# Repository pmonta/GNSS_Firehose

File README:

Design files for a wideband GNSS front-end board.  Digitizes three 50 MHz RF channels, emits 2-bit samples to gigabit Ethernet (~800 Mbit/s total payload).  Includes schematic, PCB layout, HDL, and software.  Open-source licensing.

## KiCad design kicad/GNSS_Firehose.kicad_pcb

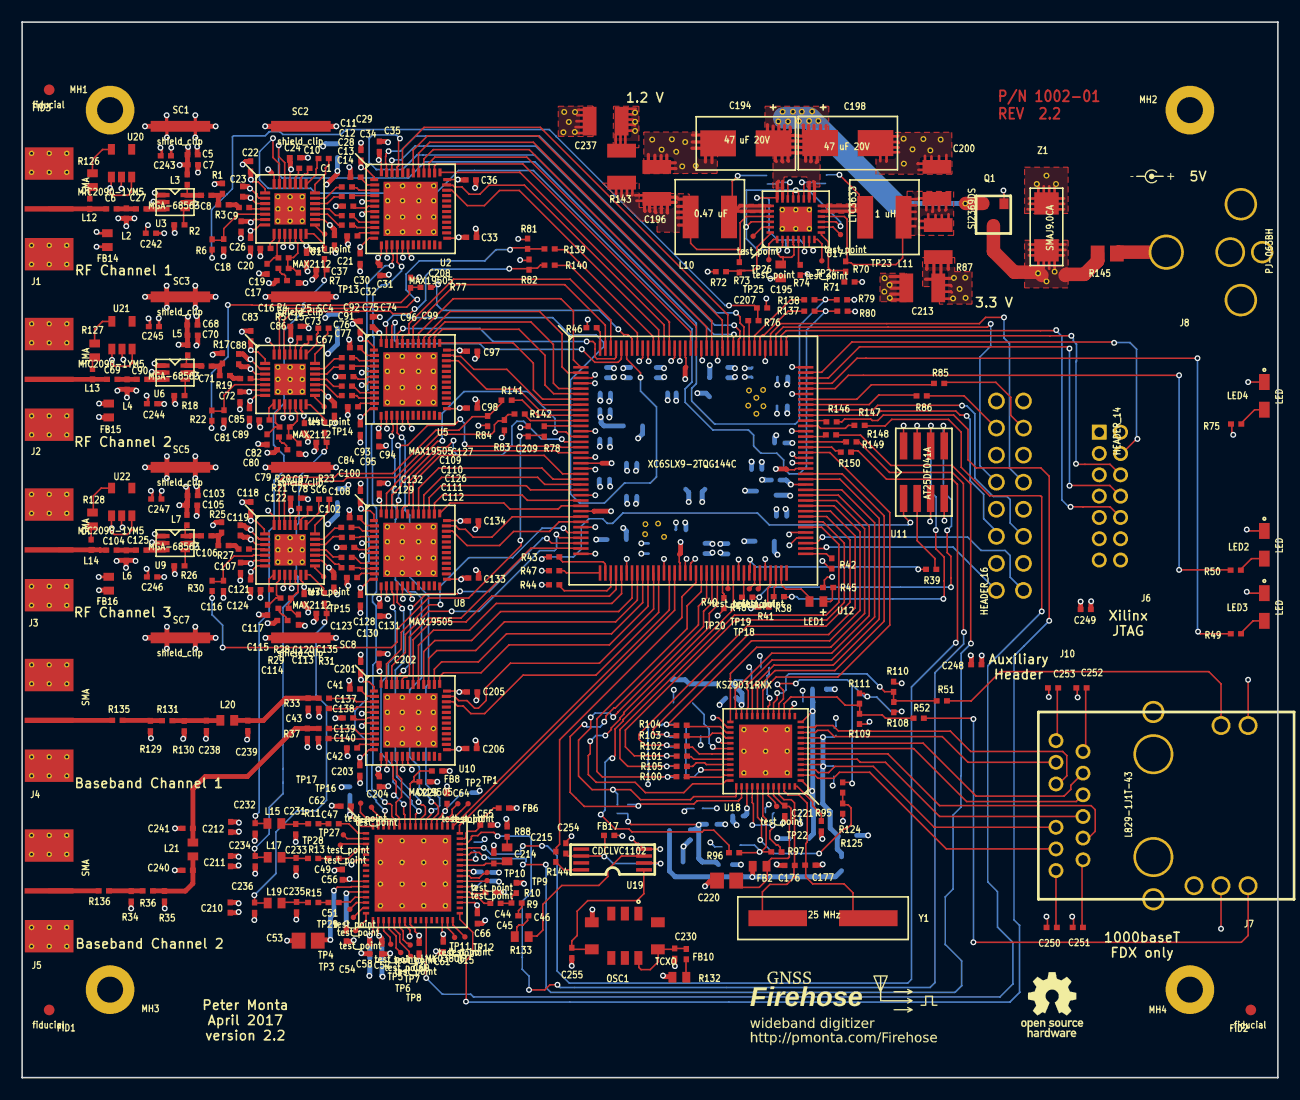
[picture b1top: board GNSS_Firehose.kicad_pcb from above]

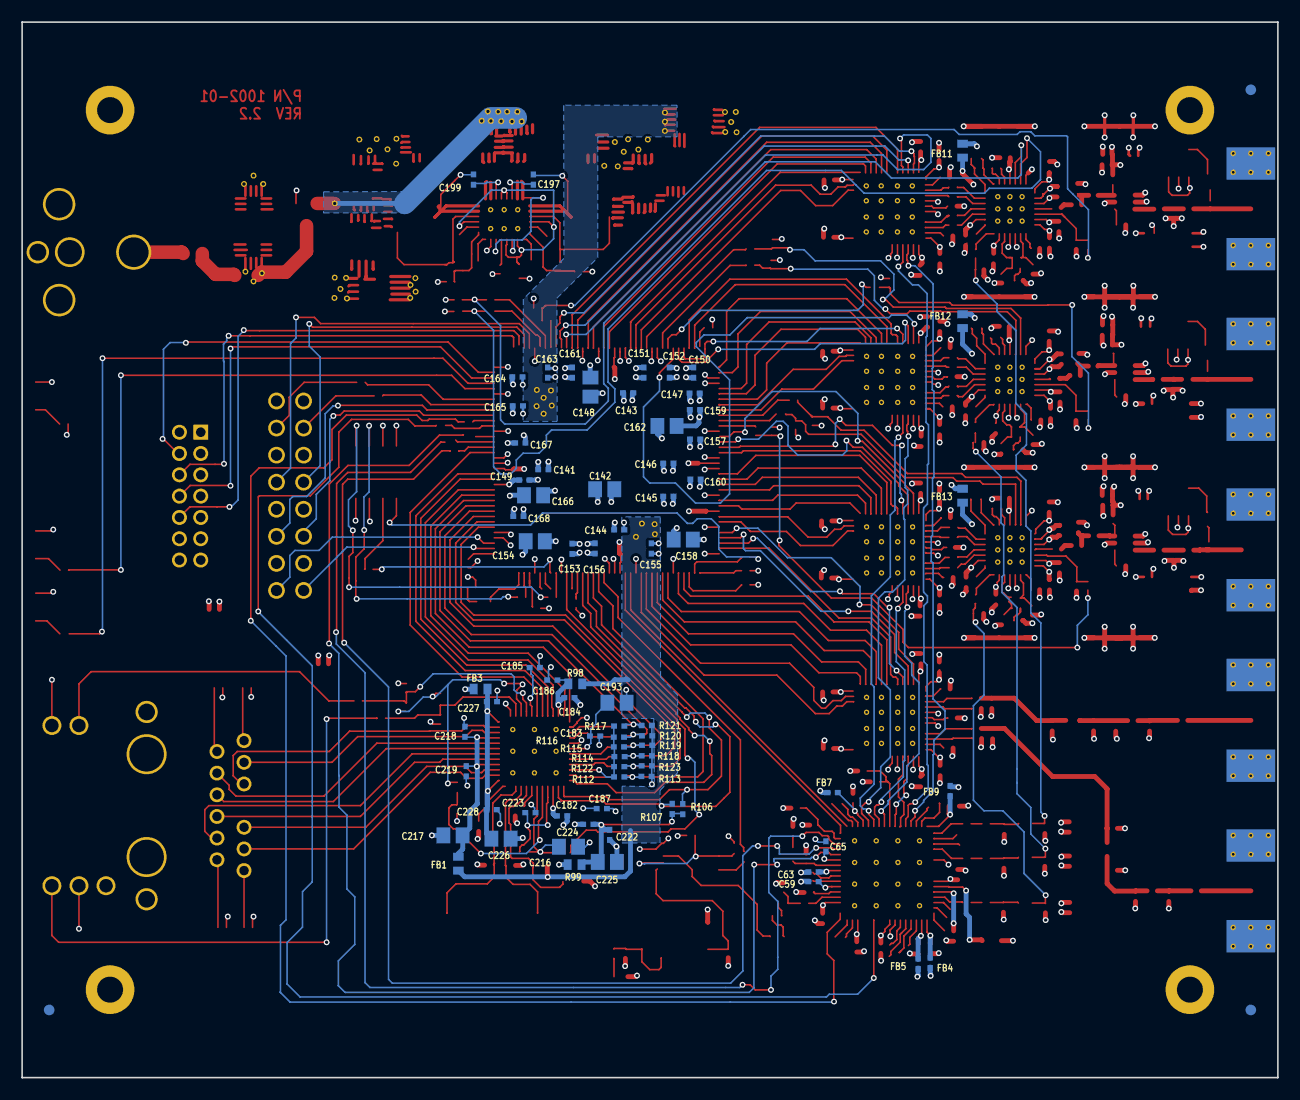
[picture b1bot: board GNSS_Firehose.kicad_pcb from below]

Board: 4 copper layers, 117.9 x 99.1 mm, 516 parts (76 on the bottom side), 362 nets.

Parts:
C1, C10, C11, C12, C13, C14, C67, C73, C74, C75, C76, C77, C102, C108, C109, C110, C111, C112: 47 nF; 0402
C5, C68, C103: 10 nF; 0402
C6, C7, C8, C9, C17, C27, C69, C70, C71, C72, C80, C90, C104, C105, C106, C107, C115, C125: 100 pF; 0402
C15, C78, C113: 2.2 nF; 0402
C16, C79, C114: 33 nF; 0402
C18, C19, C28, C29, C30, C31, C32, C33, C34, C35, C36, C37, C41, C42, C43, C44, C45, C46, C47, C49, C51, C54, C55, C56, C57, C58, C59, C60, C61, C62, C63, C64, C65, C66, C81, C82, C91, C92, C93, C94, C95, C96, C97, C98, C99, C100, C116, C117, C126, C127, C128, C129, C130, C131, C132, C133, C134, C135, C137, C138, C139, C140, C141, C143, C144, C145, C146, C147, C149, C150, C151, C152, C153, C155, C156, C157, C159, C160, C161, C163, C164, C165, C167, C168, C182, C183, C184, C185, C186, C187, C201, C202, C203, C204, C205, C206, C207, C208, C209, C210, C211, C212, C218, C219, C221, C222, C223, C224, C227, C228, C229, C230, C248, C249, C250, C251, C252, C253, C254: 0.1 uF; 0402
C20, C21, C22, C23, C24, C25, C26, C83, C84, C85, C86, C87, C88, C89, C118, C119, C120, C121, C122, C123, C124, C242, C243, C244, C245, C246, C247: 1000 pF; 0402
C53, C142, C148, C154, C158, C162, C166, C193, C216, C217, C220, C225, C226: 10 uF; 0805
C176, C177: 33 pF; 0402
C194, C198: 47 uF 20V; tantalum-size-D
C195: 2.2 uF; 0603
C196: 47 uF; 1210
C197, C199: 0.1 uF 25V; 0402
C200: 22 uF; 1210
C213, C237: NONE; 1210
C214: 220 pF; 0402
C215: 18 nF; 0603
C231, C232, C233, C234, C235, C236, C255: 10 pF; 0402
C238, C239, C240, C241: NONE; 0402
FB1, FB2, FB3, FB11, FB12, FB13, FB14, FB15, FB16: 240; 0603
FB4, FB5, FB6, FB7, FB8, FB9, FB10, FB17: 240; 0402
FID1, FID2, FID3: fiducial; FIDUCIAL
J1, J2, J3, J4, J5: SMA; SMA_END_LAUNCH
J6: HEADER_14; HEADER14_2MM
J7: L829-1J1T-43
J8: PJ-063BH
J10: HEADER_16; HEADER16_100MIL
L2, L4, L6: 6 nH; 0402
L3, L5, L7, L12, L13, L14: 47 nH; 0402
L10: 0.47 uF; NRS5020
L11: 1 uH; NRS5020
L15, L17, L19: 56 nH; 0603
L20, L21: 0; 0603
LED1: LED; 0603
LED2, LED3, LED4: LED; APA2106
MH1, MH2, MH3, MH4: mounting_hole; HOLE_UNC_2_56
OSC1: TCXO; D75J
Q1: Si2369DS; SOT23
R1, R17, R25: 86.6; 0402
R2, R18, R26: 5.1k; 0402
R3, R19, R27: 43.2; 0402
R4, R20, R28, R88: 820; 0402
R5, R21, R29: 390; 0402
R6, R22, R30, R46, R72, R73, R76, R77, R78, R79, R80, R81, R82, R83, R84, R97, R116, R117, R124, R146, R147, R148, R149, R150: 10k; 0402
R7, R11, R13, R15, R23, R31: 80; 0402
R9: 150; 0402
R10, R51, R52: 220; 0402
R33, R37: 49.9; 0402
R34, R35: 60.4; 0402
R36: 249; 0402
R38, R39, R43, R48: 47; 0402
R40, R41, R86, R106, R109, R110, R113, R118, R119, R123, R137, R138, R139, R140, R141, R142: 1k; 0402
R42, R131, R135, R136: 0; 0402
R44, R47, R107: 4.7k; 0402
R45, R49, R50, R75, R85: 330; 0402
R70: 54.9k; 0402
R71: 12.1k; 0402
R74: 162k; 0402
R87, R143: 0; 1210
R95: 12.1k 1%; 0402
R96: 470; 0402
R98, R99, R126, R127, R128, R132: 0; 0603
R100, R101, R102, R103, R104, R105: 33; 0402
R108, R111, R112, R114, R115, R120, R121, R122, R125, R129, R130: NONE; 0402
R133: 10; 0603
R144: 10; 0402
R145: 0; 0805
SC1, SC2, SC3, SC4, SC5, SC6, SC7, SC8: shield_clip; S1721
TP1, TP2, TP3, TP4, TP5, TP6, TP7, TP8, TP9, TP10, TP11, TP12, TP13, TP14, TP15, TP16, TP17, TP18, TP19, TP20, TP22, TP23, TP24, TP25, TP26, TP27, TP28, TP29: test_point; TP_SMT
U1, U4, U7: MAX2112; QFN28_EP
U2, U5, U8, U10: MAX19505; QFN48_EP
U3, U6, U9: MGA-68563; SOT-363
U11: AT25DF041A; SO8
U12: XC6SLX9-2TQG144C; LQFP144
U15: LMK03806; LLP64_EP
U17: LTC3633; UFD28
U18: KSZ9031RNX; QFN48_EP_MICREL
U19: CDCLVC1102; TSSOP8W
U20, U21, U22: MIC2090-1YM5; SOT-23-5
VIA**: via_12mil
VIA**#2, VIA**#3, VIA**#4, VIA**#5, VIA**#6, VIA**#7, VIA**#8, VIA**#9, VIA**#10, VIA**#11, VIA**#12, VIA**#13, VIA**#14, VIA**#15, VIA**#16, VIA**#17, VIA**#18, VIA**#19, VIA**#20, VIA**#21, VIA**#22, VIA**#23, VIA**#24, VIA**#25, VIA**#26, VIA**#27, VIA**#28, VIA**#29, VIA**#30, VIA**#31, VIA**#32, VIA**#33, VIA**#34, VIA**#35, VIA**#36, VIA**#37, VIA**#38, VIA**#39, VIA**#40, VIA**#41, VIA**#42, VIA**#43, VIA**#44, VIA**#45, VIA**#46, VIA**#47, VIA**#48, VIA**#49, VIA**#50, VIA**#51, VIA**#52, VIA**#53, VIA**#54, VIA**#55, VIA**#56: via_12mil
Y1: 25 MHz; CTS_ATS
Z1: SMAJ9.0CA; SMAJ

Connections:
/Clock generation/ch1_d+: C47.1, U15.1
/Clock generation/ch2_d+: C49.1, U15.4
/Clock generation/ch3_d+: C51.1, U15.13
/Ethernet/AVDDH: C226.1, C227.1, C228.1, FB3.2, U18.1, U18.12
/Ethernet/AVDDL: C217.1, C218.1, C219.1, FB1.2, U18.4, U18.9
/Ethernet/AVDDL_PLL: C220.1, C221.1, FB2.2, U18.44
/Ethernet/DVDDH: C222.1, C223.1, C224.1, C225.1, R97.1, R99.2, R106.1, R107.1, R108.1, R111.1, R112.1, R114.1, R115.1, R116.1, R117.1, R122.1, R124.1, U18.16, U18.34, U18.40
/Ethernet/DVDDL: C182.1, C183.1, C184.1, C185.1, C186.1, C187.1, C193.1, R98.2, U18.14, U18.18, U18.23, U18.26, U18.30, U18.39
/Ethernet/LED_MODE: R124.2, R125.1, U18.41
/Ethernet/chassis_gnd: J7.18, J7.19
/Ethernet/ct1: C250.1, J7.12
/Ethernet/ct2: C251.1, J7.6
/Ethernet/ct3: C252.1, J7.1
/Ethernet/ct4: C253.1, J7.7
/Ethernet/phyad0: R51.1, R108.2, R110.1, U18.17
/Ethernet/phyad1: R52.1, R109.1, R111.2, U18.15
/Ethernet/xtal1: C177.1, U18.46, Y1.1
/Ethernet/xtal2: C176.1, U18.45, Y1.2
/FPGA/CH1_GC1: R76.1, U12.116
/FPGA/CH2_GC1: R77.1, U12.138
/FPGA/CH3_GC1: R78.1, U12.12
/FPGA/TCK: J6.6, U12.109
/FPGA/TDI: J6.10, U12.110
/FPGA/TDO: J6.8, U12.106
/FPGA/TMS: J6.4, U12.107
/FPGA/UART_RX: R86.2, U12.101
/FPGA/UART_TX: R85.1, U12.102
/FPGA/cclk: R38.1, U12.70
/FPGA/cso_b: R43.1, U12.38
/FPGA/din: R39.1, U12.65
/FPGA/init_b: R44.1, U12.39
/FPGA/led0: R49.1, U12.105
/FPGA/led1: R50.1, U12.104
/FPGA/m0: R41.1, U12.69
/FPGA/m1: R40.1, U12.60
/FPGA/mosi: R48.1, U12.64
/FPGA/spare1_n: J10.2, U12.74
/FPGA/spare1_p: J10.1, U12.75
/FPGA/spare2_n: J10.6, U12.99
/FPGA/spare2_p: J10.5, U12.100
/FPGA/spare3_n: J10.10, U12.111
/FPGA/spare3_p: J10.9, U12.112
/RF Channel 2/ch2_cpout: C78.1, R20.2, R21.1, U4.12
/RF Channel 2/ch2_gc1_lpf: C81.1, R22.1, U4.5
/RF Channel 2/ch2_vcc: C83.1, C84.1, C85.1, C86.1, C87.1, C88.1, C89.1, FB12.2, U4.1, U4.2, U4.6, U4.7, U4.13, U4.16, U4.25
/RF Channel 2/ch2_vcc_lna: C68.1, C70.1, C244.1, C245.1, FB15.2, L5.1, R18.1, U21.1, U21.3
/RF Channel 2/ch2_vtune: C80.1, R20.1, U4.9
/RF Channel 2/ch2_xtal: C100.2, U4.14
/RF Channel 3/ch3_cpout: C113.1, R28.2, R29.1, U7.12
/RF Channel 3/ch3_gc1_lpf: C116.1, R30.1, U7.5
/RF Channel 3/ch3_vcc: C118.1, C119.1, C120.1, C121.1, C122.1, C123.1, C124.1, FB13.2, U7.1, U7.2, U7.6, U7.7, U7.13, U7.16, U7.25
/RF Channel 3/ch3_vcc_lna: C103.1, C105.1, C246.1, C247.1, FB16.2, L7.1, R26.1, U22.1, U22.3
/RF Channel 3/ch3_vtune: C115.1, R28.1, U7.9
/RF Channel 3/ch3_xtal: C135.2, U7.14
/RF Channel 4/10_MHz+: C137.2, U10.3
/RF Channel 4/10_MHz-: C138.2, U10.4
/RF Channel 4/PPS+: C139.2, U10.9
/RF Channel 4/PPS-: C140.2, U10.10
/RF channel 1/ch1_cpout: C15.1, R4.2, R5.1, U1.12
/RF channel 1/ch1_gc1_lpf: C18.1, R6.1, U1.5
/RF channel 1/ch1_vcc: C20.1, C21.1, C22.1, C23.1, C24.1, C25.1, C26.1, FB11.2, U1.1, U1.2, U1.6, U1.7, U1.13, U1.16, U1.25
/RF channel 1/ch1_vcc_lna: C5.1, C7.1, C242.1, C243.1, FB14.2, L3.1, R2.1, U20.1, U20.3
/RF channel 1/ch1_vtune: C17.1, R4.1, U1.9
/RF channel 1/ch1_xtal: C37.2, U1.14
CH1_CLK: U2.44, U12.120
CH1_CLK+: U2.15, U15.61
CH1_CLK-: U2.16, U15.60
CH1_CS: U2.47, U12.117
CH1_D0: U2.34, U12.133
CH1_D1: U2.35, U12.132
CH1_D2: U2.37, U12.131
CH1_D3: U2.38, U12.127
CH1_D4: U2.39, U12.126
CH1_D5: U2.40, U12.124
CH1_D6: U2.41, U12.123
CH1_D7: U2.42, U12.121
CH1_GC1_FPGA_LPF: C207.1, R6.2, R76.2
CH1_REF+: C37.1, C232.1, L15.2, R7.1
CH1_SCL: R80.2, R137.1, U1.27
CH1_SCLK: U2.46, U12.118
CH1_SDA: R79.2, R138.1, U1.26
CH1_SDIN: U2.45, U12.119
CH2_CLK: U5.44, U12.142
CH2_CLK+: U5.15, U15.53
CH2_CLK-: U5.16, U15.54
CH2_CS: U5.47, U12.139
CH2_D0: U5.34, U12.9
CH2_D1: U5.35, U12.8
CH2_D2: U5.37, U12.7
CH2_D3: U5.38, U12.6
CH2_D4: U5.39, U12.5
CH2_D5: U5.40, U12.2
CH2_D6: U5.41, U12.1
CH2_D7: U5.42, U12.143
CH2_GC1_FPGA_LPF: C208.1, R22.2, R77.2
CH2_REF+: C100.1, C234.1, L17.2, R23.1
CH2_SCL: R82.2, R139.1, U4.27
CH2_SCLK: U5.46, U12.140
CH2_SDA: R81.2, R140.1, U4.26
CH2_SDIN: U5.45, U12.141
CH3_CLK: U8.44, U12.17
CH3_CLK+: U8.15, U15.56
CH3_CLK-: U8.16, U15.55
CH3_CS: U8.47, U12.14
CH3_D0: U8.34, U12.30
CH3_D1: U8.35, U12.29
CH3_D2: U8.37, U12.27
CH3_D3: U8.38, U12.26
CH3_D4: U8.39, U12.24
CH3_D5: U8.40, U12.23
CH3_D6: U8.41, U12.22
CH3_D7: U8.42, U12.21
CH3_GC1_FPGA_LPF: C209.1, R30.2, R78.2
CH3_REF+: C135.1, C236.1, L19.2, R31.1
CH3_SCL: R84.2, R141.2, U7.27
CH3_SCLK: U8.46, U12.15
CH3_SDA: R83.2, R142.2, U7.26
CH3_SDIN: U8.45, U12.16
CH4_CLK: U10.44, U12.35
CH4_CLK+: U10.15, U15.58
CH4_CLK-: U10.16, U15.59
CH4_CS: U10.47, U12.32
CH4_D0: U10.34, U12.48
CH4_D1: U10.35, U12.47
CH4_D2: U10.37, U12.46
CH4_D3: U10.38, U12.45
CH4_D4: U10.39, U12.44
CH4_D5: U10.40, U12.43
CH4_D6: U10.41, U12.41
CH4_D7: U10.42, U12.40
CH4_SCLK: U10.46, U12.33
CH4_SDIN: U10.45, U12.34
CLK_3888: R144.2, U12.55
CLOCK_CLK: R150.1, U15.45
CLOCK_DATA: R149.1, U15.46
CLOCK_FTEST_LD: R146.1, U15.33
CLOCK_LE: R148.1, U15.44
CLOCK_READBACK: R147.1, U15.27
FPGA_CLK+: U12.51, U15.48
FPGA_CLK-: U12.50, U15.49
GND: C5.2, C7.2, C15.2, C16.2, C17.2, C18.2, C19.2, C20.2, C21.2, C22.2, C23.2, C24.2, C25.2, C26.2, C28.2, C29.2, C30.2, C31.2, C32.2, C33.2, C34.2, C35.2, C36.2, C41.2, C42.2, C43.2, C44.1, C53.2, C54.2, C55.2, C56.2, C57.2, C58.2, C59.2, C60.2, C61.2, C62.2, C63.2, C64.2, C65.2, C66.2, C68.2, C70.2, C78.2, C79.2, C80.2, C81.2, C82.2, C83.2, C84.2, C85.2, C86.2, C87.2, C88.2, C89.2, C91.2, C92.2, C93.2, C94.2, C95.2, C96.2, C97.2, C98.2, C99.2, C103.2, C105.2, C113.2, C114.2, C115.2, C116.2, C117.2, C118.2, C119.2, C120.2, C121.2, C122.2, C123.2, C124.2, C126.2, C127.2, C128.2, C129.2, C130.2, C131.2, C132.2, C133.2, C134.2, C138.1, C140.1, C141.2, C142.2, C143.2, C144.2, C145.2, C146.2, C147.2, C148.2, C149.2, C150.2, C151.2, C152.2, C153.2, C154.2, C155.2, C156.2, C157.2, C158.2, C159.2, C160.2, C161.2, C162.2, C163.2, C164.2, C165.2, C166.2, C167.2, C168.2, C176.2, C177.2, C182.2, C183.2, C184.2, C185.2, C186.2, C187.2, C193.2, C194.2, C195.2, C196.2, C198.2, C200.2, C201.2, C202.2, C203.2, C204.2, C205.2, C206.2, C207.2, C208.2, C209.2, C210.2, C211.2, C212.2, C213.2, C214.2, C216.2, C217.2, C218.2, C219.2, C220.2, C221.2, C222.2, C223.2, C224.2, C225.2, C226.2, C227.2, C228.2, C229.2, C230.2, C231.2, C232.2, C233.2, C234.2, C235.2, C236.2, C237.2, C238.2, C239.2, C240.2, C241.2, C242.2, C243.2, C244.2, C245.2, C246.2, C247.2, C248.2, C249.2, C250.2, C251.2, C252.2, C253.2, C254.2, C255.2, J1.2, J2.2, J3.2, J4.2, J5.2, J6.1, J6.3, J6.5, J6.7, J6.9, J6.11, J6.13, J8.2, J10.7, J10.8, J10.11, J10.12, J10.15, J10.16, L2.2, L4.2, L6.2, LED2.2, LED3.2, LED4.2, MH1.1, MH2.1, MH3.1, MH4.1, OSC1.4, Q1.1, R1.2, R7.2, R10.2, R17.2, R23.2, R25.2, R31.2, R33.2, R34.2, R35.2, R37.2, R40.2, R42.2, R46.1, R71.2, R72.2, R74.2, R88.2, R95.2, R109.2, R110.2, R113.2, R118.2, R119.2, R120.2, R121.2, R123.2, R125.2, R129.2, R130.2, SC1.1, SC2.1, SC3.1, SC4.1, SC5.1, SC6.1, SC7.1, SC8.1, U1.3, U1.10, U1.11, U1.28, U1.29, U2.5, U2.7, U2.14, U2.17, U2.18, U2.49, U3.1, U3.2, U3.5, U4.3, U4.10, U4.11, U4.28, U4.29, U5.5, U5.7, U5.14, U5.17, U5.18, U5.49, U6.1, U6.2, U6.5, U7.3, U7.10, U7.11, U7.28, U7.29, U8.5, U8.7, U8.14, U8.17, U8.18, U8.49, U9.1, U9.2, U9.5, U10.5, U10.7, U10.14, U10.17, U10.18, U10.49, U11.4, U12.3, U12.13, U12.25, U12.49, U12.54, U12.68, U12.77, U12.91, U12.96, U12.108, U12.113, U12.130, U12.136, U15.6, U15.23, U15.65, U17.7, U17.29, U18.29, U18.49, U19.4, U20.2, U21.2, U22.2, VIA**#19.1, VIA**#20.1, VIA**#21.1, VIA**#22.1, VIA**#23.1, VIA**#24.1, VIA**#25.1, VIA**#26.1, VIA**#33.1, VIA**#34.1, VIA**#35.1, VIA**#36.1, VIA**#37.1, VIA**#38.1, VIA**#39.1, VIA**#40.1, VIA**#41.1, VIA**#42.1, VIA**#43.1, VIA**#44.1, VIA**#45.1, VIA**#49.1, VIA**#50.1, VIA**#52.1, VIA**#54.1, Z1.2
unnamed: C1.1, U1.22
unnamed: C1.2, U1.21
unnamed: C6.1, J1.1, L12.2
unnamed: C8.1, L3.2, U3.6
unnamed: C8.2, R1.1, R3.2
unnamed: C9.1, R3.1
unnamed: C9.2, U1.4
unnamed: C10.1, U1.24
unnamed: C10.2, U1.23
unnamed: C11.1, U1.20
unnamed: C11.2, U2.3
unnamed: C12.1, U1.19
unnamed: C12.2, U2.4
unnamed: C13.1, U1.18
unnamed: C13.2, U2.9
unnamed: C14.1, U1.17
unnamed: C14.2, U2.10
unnamed: C16.1, R5.2
unnamed: C19.1, U1.8
unnamed: C6.2, C27.1, L2.1
unnamed: C27.2, U3.3
unnamed: C28.1, U2.6
unnamed: C29.1, U2.2
unnamed: C30.1, U2.11
unnamed: C41.1, U10.2
unnamed: C42.1, U10.11
unnamed: C43.1, U10.6
unnamed: C44.2, U15.37
unnamed: C45.1, R9.2, R10.1
unnamed: C45.2, U15.36
unnamed: C46.1, R133.2
unnamed: C46.2, R9.1
unnamed: C47.2, R11.1
unnamed: C49.2, R13.1
unnamed: C51.2, R15.1
unnamed: C53.1, U15.11
unnamed: C54.1, U15.12
unnamed: C55.1, FB6.2, U15.47
unnamed: C57.1, FB5.2, U15.18
unnamed: C58.1, FB4.2, U15.17
unnamed: C62.1, FB9.2, U15.64
unnamed: C64.1, FB7.2, U15.52
unnamed: C67.1, U4.22
unnamed: C67.2, U4.21
unnamed: C69.1, J2.1, L13.2
unnamed: C69.2, C90.1, L4.1
unnamed: C71.1, L5.2, U6.6
unnamed: C71.2, R17.1, R19.2
unnamed: C72.1, R19.1
unnamed: C72.2, U4.4
unnamed: C73.1, U4.24
unnamed: C73.2, U4.23
unnamed: C74.1, U4.20
unnamed: C74.2, U5.3
unnamed: C75.1, U4.19
unnamed: C75.2, U5.4
unnamed: C76.1, U4.18
unnamed: C76.2, U5.9
unnamed: C77.1, U4.17
unnamed: C77.2, U5.10
unnamed: C79.1, R21.2
unnamed: C82.1, U4.8
unnamed: C90.2, U6.3
unnamed: C91.1, U5.6
unnamed: C92.1, U5.2
unnamed: C93.1, U5.11
unnamed: C102.1, U7.22
unnamed: C102.2, U7.21
unnamed: C104.1, J3.1, L14.2
unnamed: C104.2, C125.1, L6.1
unnamed: C106.1, L7.2, U9.6
unnamed: C106.2, R25.1, R27.2
unnamed: C107.1, R27.1
unnamed: C107.2, U7.4
unnamed: C108.1, U7.24
unnamed: C108.2, U7.23
unnamed: C109.1, U7.20
unnamed: C109.2, U8.3
unnamed: C110.1, U7.19
unnamed: C110.2, U8.4
unnamed: C111.1, U7.18
unnamed: C111.2, U8.9
unnamed: C112.1, U7.17
unnamed: C112.2, U8.10
unnamed: C114.1, R29.2
unnamed: C117.1, U7.8
unnamed: C125.2, U9.3
unnamed: C126.1, U8.6
unnamed: C127.1, U8.2
unnamed: C128.1, U8.11
unnamed: C137.1, C239.1, L20.2, R33.1
unnamed: C139.1, C241.1, L21.2, R37.1
unnamed: C194.1, C198.1, Q1.2, U17.3, U17.6, U17.15, U17.16, U17.21, U17.22, VIA**#9.1, VIA**#10.1, VIA**#11.1, VIA**#12.1, VIA**#13.1, VIA**#14.1, VIA**#15.1, VIA**#16.1, VIA**#46.1, VIA**#51.1
unnamed: C195.1, U17.2, U17.4, U17.11, U17.18, U17.19, U17.26
unnamed: C196.1, L10.2, R73.2, R143.1, U17.25
unnamed: C197.1, L10.1, U17.23, U17.24
unnamed: C197.2, U17.20
unnamed: C199.1, U17.17
unnamed: C199.2, L11.2, U17.13, U17.14
unnamed: C200.1, L11.1, R70.1, R87.2, U17.12
unnamed: C214.1, C215.1, U15.42
unnamed: C215.2, R88.1
unnamed: C216.1, R96.2, R97.2, U18.42
unnamed: C229.1, FB8.2, U15.57
unnamed: C230.1, FB10.2, OSC1.8, OSC1.9
unnamed: C231.1, L15.1, R11.2
unnamed: C233.1, L17.1, R13.2
unnamed: C235.1, L19.1, R15.2
unnamed: C238.1, L20.1, R130.1, R131.2
unnamed: C240.1, L21.1, R35.1, R36.2
unnamed: C254.1, FB17.2, U19.2, U19.6
unnamed: C255.1, OSC1.5, U19.1
unnamed: FB10.1, R132.2
unnamed: J4.1, R135.1
unnamed: J5.1, R136.1
unnamed: J7.2, U18.8
unnamed: J7.3, U18.7
unnamed: J7.4, U18.5
unnamed: J7.5, U18.6
unnamed: J7.8, U18.10
unnamed: J7.9, U18.11
unnamed: J7.10, U18.3
unnamed: J7.11, U18.2
unnamed: J7.13, R51.2
unnamed: J7.17, R52.2
unnamed: J8.1, R145.1
unnamed: J10.13, R85.2
unnamed: J10.14, R86.1
unnamed: L12.1, R126.1
unnamed: L13.1, R127.1
unnamed: L14.1, R128.1
unnamed: LED1.1, R45.1
unnamed: LED1.2, U12.71
unnamed: LED2.1, R50.2
unnamed: LED3.1, R49.2
unnamed: LED4.1, R75.2
unnamed: Q1.3, R145.2, VIA**#31.1, VIA**#32.1, VIA**#47.1, Z1.1
unnamed: R2.2, U3.4
unnamed: R18.2, U6.4
unnamed: R26.2, U9.4
unnamed: R38.2, U11.6
unnamed: R39.2, U11.2
unnamed: R42.1, U12.73
unnamed: R43.2, U11.1
unnamed: R46.2, U12.144
unnamed: R47.1, U12.37
unnamed: R48.2, U11.5
unnamed: R70.2, R71.1, U17.9
unnamed: R72.1, R73.1, U17.28
unnamed: R74.1, U17.5
unnamed: R95.1, U18.48
unnamed: R100.2, U18.35
unnamed: R101.2, U18.32
unnamed: R102.2, U18.31
unnamed: R103.2, U18.28
unnamed: R104.2, U18.27
unnamed: R105.2, U18.33
unnamed: R126.2, U20.5
unnamed: R127.2, U21.5
unnamed: R128.2, U22.5
unnamed: R129.1, R131.1, R135.2
unnamed: R133.1, U19.3
unnamed: R34.1, R36.1, R136.2
unnamed: R137.2, U12.114
unnamed: R138.2, U12.115
unnamed: R139.2, U12.134
unnamed: R140.2, U12.137
unnamed: R141.1, U12.10
unnamed: R142.1, U12.11
unnamed: R144.1, U19.8
unnamed: R146.2, U12.98
unnamed: R147.2, U12.97
unnamed: R148.2, U12.95
unnamed: R149.2, U12.94
unnamed: R150.2, U12.93
unnamed: TP1.1, U15.50
unnamed: TP2.1, U15.51
unnamed: TP3.1, U15.16
unnamed: TP4.1, U15.15
unnamed: TP5.1, U15.19
unnamed: TP6.1, U15.20
unnamed: TP7.1, U15.22
unnamed: TP8.1, U15.21
unnamed: TP9.1, U15.39
unnamed: TP10.1, U15.40
unnamed: TP11.1, U15.31
unnamed: TP12.1, U15.32
unnamed: TP13.1, U1.15
unnamed: TP14.1, U4.15
unnamed: TP15.1, U7.15
unnamed: TP16.1, U15.62
unnamed: TP17.1, U15.63
unnamed: TP18.1, U12.67
unnamed: TP19.1, U12.66
unnamed: TP20.1, U12.61
unnamed: TP22.1, U18.43
unnamed: TP23.1, U17.10
unnamed: TP24.1, U17.8
unnamed: TP25.1, U17.27
unnamed: TP26.1, U17.1
unnamed: TP27.1, U15.2
unnamed: TP28.1, U15.3
unnamed: TP29.1, U15.14
PHY_MDC: U12.59, U18.36
PHY_MDINT: R107.2, U12.57, U18.38
PHY_MDIO: R106.2, U12.58, U18.37
PHY_NRESET: R96.1, U12.62
PHY_RXD0: R101.1, R114.2, R118.1, U12.79
PHY_RXD1: R102.1, R115.2, R119.1, U12.80
PHY_RXD2: R103.1, R116.2, R120.1, U12.81
PHY_RXD3: R104.1, R117.2, R121.1, U12.82
PHY_RX_CLK: R100.1, R112.2, R113.1, U12.56
PHY_RX_CTL: R105.1, R122.2, R123.1, U12.78
PHY_TXD0: U12.92, U18.19
PHY_TXD1: U12.88, U18.20
PHY_TXD2: U12.87, U18.21
PHY_TXD3: U12.85, U18.22
PHY_TX_CLK: U12.84, U18.24
PHY_TX_CTL: U12.83, U18.25
VCC_1.2V: C141.1, C142.1, C143.1, C144.1, C145.1, C146.1, C237.1, FB1.1, FB2.1, R98.1, R143.2, U12.19, U12.28, U12.52, U12.89, U12.128, VIA**.1, VIA**#2.1, VIA**#3.1, VIA**#4.1, VIA**#5.1, VIA**#6.1, VIA**#7.1, VIA**#8.1, VIA**#17.1, VIA**#18.1, VIA**#53.1, VIA**#55.1, VIA**#56.1
VCC_3.3V: C31.1, C32.1, C33.1, C34.1, C35.1, C36.1, C56.1, C59.1, C60.1, C61.1, C63.1, C65.1, C66.1, C94.1, C95.1, C96.1, C97.1, C98.1, C99.1, C129.1, C130.1, C131.1, C132.1, C133.1, C134.1, C147.1, C148.1, C149.1, C150.1, C151.1, C152.1, C153.1, C154.1, C155.1, C156.1, C157.1, C158.1, C159.1, C160.1, C161.1, C162.1, C163.1, C164.1, C165.1, C166.1, C167.1, C168.1, C201.1, C202.1, C203.1, C204.1, C205.1, C206.1, C210.1, C211.1, C212.1, C213.1, C248.1, C249.1, FB3.1, FB4.1, FB5.1, FB6.1, FB7.1, FB8.1, FB9.1, FB11.1, FB12.1, FB13.1, FB14.1, FB15.1, FB16.1, FB17.1, J6.2, J7.14, J7.16, J10.3, J10.4, R41.2, R44.2, R45.2, R47.2, R75.1, R79.1, R80.1, R81.1, R82.1, R83.1, R84.1, R87.1, R99.1, R132.1, U2.1, U2.12, U2.13, U2.25, U2.36, U2.48, U5.1, U5.12, U5.13, U5.25, U5.36, U5.48, U8.1, U8.12, U8.13, U8.25, U8.36, U8.48, U10.1, U10.12, U10.13, U10.25, U10.36, U10.48, U11.3, U11.7, U11.8, U12.4, U12.18, U12.20, U12.31, U12.36, U12.42, U12.53, U12.63, U12.76, U12.86, U12.90, U12.103, U12.122, U12.125, U12.129, U12.135, U15.10, U15.24, U15.30, U15.35, U15.38, U15.41, U15.43, VIA**#27.1, VIA**#28.1, VIA**#29.1, VIA**#30.1, VIA**#48.1

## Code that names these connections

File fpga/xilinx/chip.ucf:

# FPGA timing and pin-location constraints
#
# GNSS Firehose
# Copyright (c) 2012 Peter Monta <pmonta@gmail.com>

# Try to follow UG625.
# UG612 covers how to put similar info into a separate .sdc tcl file.
net "clk_adc" tnm_net = "clkADC";
timespec "ts_clkADC" = period "clkADC" 14.5ns;

net "phy_rx_clk" tnm_net = "clkPHYrx";
timespec "ts_clkPHYrx" = period "clkPHYrx" 8ns;

net "clk_3888" tnm_net = "clkTCXO";
timespec "ts_clkTCXO" = period "clkTCXO" 25.72ns;

net "clk125" tnm_net = "clkPHYtx";
timespec "ts_clkPHYtx" = period "clkPHYtx" 8ns;

timegrp "ADC_part" = "clkADC";
timegrp "ETH_part" = "clkPHYtx" "clk125_dcm";
timegrp "CPU_part" = "clkTCXO" EXCEPT "clk125_dcm";

net clk_adc_p loc=p51 | iostandard=lvds_33 | diff_term="true" ;
net clk_adc_n loc=p50 | iostandard=lvds_33 | diff_term="true" ;
net clk_3888 loc=p55 | iostandard=lvcmos33 ;

net ch1_sda loc=p115  | iostandard=lvcmos33 | slew="slow" ;
net ch1_scl loc=p114  | iostandard=lvcmos33 | slew="slow" ;
net ch1_gc1 loc=p116  | iostandard=lvcmos33 | slew="slow" ;
net ch1_cs loc=p117   | iostandard=lvcmos33 | slew="slow" ;
net ch1_sclk loc=p118 | iostandard=lvcmos33 | slew="slow" ;
net ch1_sdin loc=p119 | iostandard=lvcmos33 | slew="slow" ;
net ch1_clk loc=p120  | iostandard=lvcmos33 ;
net ch1_d<0> loc=p133 | iostandard=lvcmos33 ;
net ch1_d<1> loc=p132 | iostandard=lvcmos33 ;
net ch1_d<2> loc=p131 | iostandard=lvcmos33 ;
net ch1_d<3> loc=p127 | iostandard=lvcmos33 ;
net ch1_d<4> loc=p126 | iostandard=lvcmos33 ;
net ch1_d<5> loc=p124 | iostandard=lvcmos33 ;
net ch1_d<6> loc=p123 | iostandard=lvcmos33 ;
net ch1_d<7> loc=p121 | iostandard=lvcmos33 ;

net ch2_sda loc=p137  | iostandard=lvcmos33 | slew="slow" ;
net ch2_scl loc=p134  | iostandard=lvcmos33 | slew="slow" ;
net ch2_gc1 loc=p138  | iostandard=lvcmos33 | slew="slow" ;
net ch2_cs loc=p139   | iostandard=lvcmos33 | slew="slow" ;
net ch2_sclk loc=p140 | iostandard=lvcmos33 | slew="slow" ;
net ch2_sdin loc=p141 | iostandard=lvcmos33 | slew="slow" ;
net ch2_clk loc=p142  | iostandard=lvcmos33 ;
net ch2_d<0> loc=p9   | iostandard=lvcmos33 ;
net ch2_d<1> loc=p8   | iostandard=lvcmos33 ;
net ch2_d<2> loc=p7   | iostandard=lvcmos33 ;
net ch2_d<3> loc=p6   | iostandard=lvcmos33 ;
net ch2_d<4> loc=p5   | iostandard=lvcmos33 ;
net ch2_d<5> loc=p2   | iostandard=lvcmos33 ;
net ch2_d<6> loc=p1   | iostandard=lvcmos33 ;
net ch2_d<7> loc=p143 | iostandard=lvcmos33 ;

net ch3_sda loc=p11   | iostandard=lvcmos33 | slew="slow" ;
net ch3_scl loc=p10   | iostandard=lvcmos33 | slew="slow" ;
net ch3_gc1 loc=p12   | iostandard=lvcmos33 | slew="slow" ;
net ch3_cs loc=p14    | iostandard=lvcmos33 | slew="slow" ;
net ch3_sclk loc=p15  | iostandard=lvcmos33 | slew="slow" ;
net ch3_sdin loc=p16  | iostandard=lvcmos33 | slew="slow" ;
net ch3_clk loc=p17   | iostandard=lvcmos33 ;
net ch3_d<0> loc=p30  | iostandard=lvcmos33 ;
net ch3_d<1> loc=p29  | iostandard=lvcmos33 ;
net ch3_d<2> loc=p27  | iostandard=lvcmos33 ;
net ch3_d<3> loc=p26  | iostandard=lvcmos33 ;
net ch3_d<4> loc=p24  | iostandard=lvcmos33 ;
net ch3_d<5> loc=p23  | iostandard=lvcmos33 ;
net ch3_d<6> loc=p22  | iostandard=lvcmos33 ;
net ch3_d<7> loc=p21  | iostandard=lvcmos33 ;

net ch4_cs loc=p32    | iostandard=lvcmos33 | slew="slow" ;
net ch4_sclk loc=p33  | iostandard=lvcmos33 | slew="slow" ;
net ch4_sdin loc=p34  | iostandard=lvcmos33 | slew="slow" ;
net ch4_clk loc=p35   | iostandard=lvcmos33 ;
net ch4_d<0> loc=p48  | iostandard=lvcmos33 ;
net ch4_d<1> loc=p47  | iostandard=lvcmos33 ;
net ch4_d<2> loc=p46  | iostandard=lvcmos33 ;
net ch4_d<3> loc=p45  | iostandard=lvcmos33 ;
net ch4_d<4> loc=p44  | iostandard=lvcmos33 ;
net ch4_d<5> loc=p43  | iostandard=lvcmos33 ;
net ch4_d<6> loc=p41  | iostandard=lvcmos33 ;
net ch4_d<7> loc=p40  | iostandard=lvcmos33 ;

net phy_tx_clk loc=p84     | iostandard=lvcmos33 ;
net phy_tx_data<0> loc=p92 | iostandard=lvcmos33 ;
net phy_tx_data<1> loc=p88 | iostandard=lvcmos33 ;
net phy_tx_data<2> loc=p87 | iostandard=lvcmos33 ;
net phy_tx_data<3> loc=p85 | iostandard=lvcmos33 ;
net phy_tx_ctl loc=p83     | iostandard=lvcmos33 ;

net phy_rx_clk loc=p56     | iostandard=lvcmos33 ;
net phy_rx_data<0> loc=p79 | iostandard=lvcmos33 ;
net phy_rx_data<1> loc=p80 | iostandard=lvcmos33 ;
net phy_rx_data<2> loc=p81 | iostandard=lvcmos33 ;
net phy_rx_data<3> loc=p82 | iostandard=lvcmos33 ;
net phy_rx_ctl loc=p78     | iostandard=lvcmos33 ;

net phy_mdc loc=p59   | iostandard=lvcmos33 | slew="slow" ;
net phy_mdio loc=p58  | iostandard=lvcmos33 | slew="slow" ;
net phy_mdint loc=p57 | iostandard=lvcmos33 ;
net phy_nreset loc=p62  | iostandard=lvcmos33 | slew="slow" ;

net clock_clk loc=p93      | iostandard=lvcmos33 | slew="slow" ;
net clock_data loc=p94     | iostandard=lvcmos33 | slew="slow" ;
net clock_le loc=p95       | iostandard=lvcmos33 | slew="slow" ;
net clock_readback loc=p97 | iostandard=lvcmos33 ;
net clock_ftest_ld loc=p98 | iostandard=lvcmos33 ;

net uart_rx loc=p101  | iostandard=lvcmos33 ;
net uart_tx loc=p102  | iostandard=lvcmos33 | slew="slow" ;

net led0 loc=p105 | iostandard=lvcmos33 | slew="slow" ;
net led1 loc=p104 | iostandard=lvcmos33 | slew="slow" ;

net spi_cclk  loc=p70 | iostandard=lvcmos33 | slew="slow" ;
net spi_din   loc=p65 | iostandard=lvcmos33 ;
net spi_mosi  loc=p64 | iostandard=lvcmos33 | slew="slow" ;
net spi_cso_b loc=p38 | iostandard=lvcmos33 | slew="slow" ;

# net spare1_p loc=p75  | iostandard=lvcmos33 ;
# net spare1_n loc=p74  | iostandard=lvcmos33 ;
# net spare2_p loc=p100 | iostandard=lvcmos33 ;
# net spare2_n loc=p99  | iostandard=lvcmos33 ;
# net spare3_p loc=p112 | iostandard=lvcmos33 ;
# net spare3_n loc=p111 | iostandard=lvcmos33 ;

# net tp18 loc=p67 | iostandard=lvcmos33 ;
# net tp19 loc=p66 | iostandard=lvcmos33 ;
# net tp20 loc=p61 | iostandard=lvcmos33 ;

# TIG == Timing IGnore
net "*streamer_enable*" tig;
net "*packet_count*" tig;
net "*activity_clk_adc*" tig;
net "*activity_phy_tx_clk*" tig;
net "*mac_addr*" tig;
net "*eth_rx_ready*" tig;
net "*eth_rx_read*" tig;
net "*eth_tx_ready*" tig;

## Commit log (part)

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2012-06-03 initial revision
2012-06-03 add a README file for github
2012-06-03 include a PDF version of the schematic
2012-06-03 more descriptive README
2012-07-02 reconfigure the PHY reset signals; give an explicit SYNC signal to the LMK03806
2012-07-02 write the proper number of zeros if tcpdump drops packets
2012-10-20 Pacoblaze source files from pacoblaze-2.2 release
2012-10-20 modify pacoblaze to be pacoblaze-3-specific, for better readability
2012-10-21 add skeleton picoblaze code; adjust CPU clock to 62.5 MHz to make timing; UART now at 115200
2012-10-21 remove some synthesis warnings
2012-10-21 working picoblaze UART demo
2012-10-21 implement the serial protocol using picoblaze
2012-10-22 working clock init from picoblaze
2012-10-23 working I2C picoblaze code; board now fully initializes from picoblaze
2012-10-23 set I2C bus speed to ~100 kbit/s
2012-10-27 add histogram hardware for automatic gain control
2012-10-27 software does AGC at powerup. board is now autonomous
2012-10-27 initialize all three RF channels; do full gain-control range just in case
2012-11-08 enclosure, 3D-printable
2012-11-08 command-line argument for skipping N packets at start of capture
2014-04-28 change Ethernet PHY to Micrel KSZ9031RNXCA add TVS diode for DC-input protection use relative paths for footprint files
2014-04-28 add footprints for bias tees at RF inputs cosmetic updates to schematic text optional attenuator on 10 MHz input
2014-04-29 add auxiliary header with FPGA and UART signals change to larger LX9 FPGA add external clock option
2014-05-03 add shield clips for optional RF shield cans revise mounting holes
2014-05-03 better bypassing for clock chip, TCXO ground the DC-input shield
2014-05-04 switch polarity of UART signals to match 3.3 V logic-level cables such as FTDI's TTL-232R-3V3 series update hw.py to respect 'port' argument
2014-05-04 add lowpass filters on downconverter reference clocks add series resistors on control lines for isolation add series element in the 1.2 V path for current measurement
2014-05-04 cosmetic schematic changes
2014-05-12 add optional LPF on baseband inputs remap FPGA pins for clean routing to new PHY improve MAX2112 bypassing remove unused refclk wires
2014-05-12 export a color PDF of the schematic in the makefile
2014-05-12 revised layout: rough placement preliminary logo
2014-05-14 separate bypassing for LNA partial placement
2014-05-17 partial routing automate CAM steps (exporting gerbers, BOM, etc.) in the makefile add fiducials
2014-05-18 more layout add shield clips around TCXO for possibly a better thermal environment logos and revised text
2014-05-20 layout complete add paste squares in PHY exposed pad
2014-05-25 HDL and pinout changes for new PHY
2014-05-28 export PDF with assembly diagram and layer images
2014-05-31 make FPGA mode-bit pullups/pulldowns stronger; 10k was too weak to correctly configure M1
2014-06-17 send PHY's clk125 to FPGA add clock activity counters and packet counter use an enable for the packet streamer: apparently need to disable packets prior to PHY link up add a PHY reset bit from CPU te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
2014-06-17 reduce "digital feedback" from ADC outputs back to RF section: change to Gray coding, reverse bit order, reduce drive strength
2014-06-17 make ADC and MAX2112 clocks the same frequency to reduce spurs; temporary clock plan for just L1
2014-06-25 add optional correction for ADC's DC offset (just channel 1 for now) reduce 3 dB bandwidth of antialias filter slightly
2014-06-26 generate PHY transmit clock using a DCM; disable PHY's clk125 output
2014-06-26 use TCXO as CPU clock
2014-07-20 python 3 compatibility
2014-08-26 small 3D-printable plastic cap for TCXO to reduce air currents
2014-09-05 reset DCM after configuring clock chip
2014-09-06 poll PHY for link status; enable packet stream only if link is up (otherwise autonegotiation stalls)
2014-09-06 close the AGC loop in software; enable by default
2014-09-10 change to fractional-n synthesis on MAX2112 final band center frequencies for L1, L2, L5
2014-09-24 add DC correction to RF channels 2 and 3
2015-03-20 change board size to 4640 x 3900 mil for compatibility with Hammond 1455L1202 enclosure
2015-03-20 adjust ground and power planes
2015-03-22 change SMA jack to panel mount adjust mounting holes and fiducials
2015-03-23 change Ethernet connector to L829-1J1T-43 (has separate center taps as required by PHY)
2015-03-25 change to right-angle LEDs, place along edge
2015-03-26 add reverse-polarity protection
2015-03-27 add buffer for TCXO remove external clock header isolation resistors for various control signals
2015-03-27 add current limiters to RF-input bias tees cosmetic: change mislabeled "2_48" mounting holes to the correct "UNC_2_56"
2015-04-04 finish PCB place and route swap FPGA pins for PHY_RX_CLK and PHY_NRESET for better on-FPGA clock routing
2015-04-04 produce PCB CAM products (gerbers, board images, xy files, assembly drawings) produce PDF schematic cosmetic silkscreen revisions
2015-04-04 new PCB CAM products
2015-04-10 change TCXO to 38.88 MHz on schematic, symbol, BOM
2015-04-14 DFM tweaks: modify 0402 footprint
2015-04-15 DFM tweaks: 0402 component spacing
2015-04-15 DFM tweaks: increase clearance for QFN exposed pads
2015-04-16 DFM tweaks: wire cleanup
2015-04-16 DFM tweaks: fixes from freedfm.com, CAM output
2015-04-19 DFM tweaks: change vias to 12 mil, enforce 5-mil soldermask dams
2015-04-19 DFM tweaks: add via plugs and primary soldermask clearance around vias (encroachment)
2015-04-21 add single-page fab and assembly drawings; update BOM
2015-04-22 final annotated BOM
2015-05-07 add internal part numbers to BOM
2015-05-07 convert tcpdump to waveform, for use in software-decoder pipelines
2015-05-09 add notes to fab drawing
2015-05-09 fix copper clearance (found by freedfm.com)
2015-05-10 minor spacing fixes. final layout
2015-05-12 at the suggestion of Advanced Circuits, change the QFN pad vias to 10 mil and plug from the bottom surface
2015-05-23 clean up constraints for clock crossings between DCM-derived clocks
2015-05-23 add trce and ngc2edif files to "make clean"
2015-05-23 tell xst not to infer 9k block RAMs, in an abundance of caution (Xilinx answer record 39999)
2015-05-26 final BOM tweaks
2015-05-27 minor BOM tweak for Digi-Key order
2015-06-04 fix minor inconsistencies in BOM
2015-06-04 add a CPU command to store into scratchpad registers
2015-06-04 temporarily remove PHY receive link
2015-06-04 add some FPGA test environments to help with progressive board bring-up
2015-06-08 revise the plastic TCXO cap
2015-06-08 restructure the BOM for cleaner interface to octopart BOM tools
2015-06-08 cosmetic HDL tweaks
2015-06-09 fix TCXO cap orientation
2015-06-11 support programmable MAC address change Ethernet typelen to 0x88b5 (local experimental use) support flash access over SPI bus for reading MAC address, calibration parameters, serial number, etc.
2015-06-12 support SPI flash reading and programming
2015-06-13 fetch MAC address from flash at power-up
2015-06-13 scripts for production programming of flash parameters
2015-06-13 SPI support routines
2015-06-19 labels for enclosure front/back/top
2015-06-19 enclosure end plates with apertures
2015-06-22 final enclosure artwork and CAD files
2015-07-08 test code for Ethernet receive additional sampling modes
2015-07-11 Ethernet interface for CPU (write-only for now)
2015-07-13 rename clk64 to clk_adc for clarity
2015-07-13 clean up redundant clk125 port
2015-12-07 Update part number for L10
2017-03-18 start changing over to KiCAD for schematic and PCB layout
2017-03-19 more KiCAD schematic
2017-03-19 start changeover from picoblaze to risc-v to enable firmware development in C
2017-03-20 have firmware blink an LED
2017-03-20 fix KiCAD power symbol
2017-03-20 schematic, RF channels 2 and 3
2017-03-23 begin translating firmware into C
2017-03-23 more C firmware
2017-03-24 finished C firmware (not yet tested)
2017-03-26 firmware fixes
2017-03-26 revert unneeded changes to stock picorv32
2017-03-26 allow readback of AGC gain values
2017-03-27 skip over non-Firehose packets in tcpdump file
2017-03-30 more KiCAD schematic: power symbols, global nets
2017-03-30 fix connections
2017-03-31 KiCAD schematic complete
2017-04-01 fix 1.2V power symbol and pin name. Netlists are now identical between gEDA and KiCAD
2017-04-01 start KiCAD layout
2017-04-02 initial placement and wires
2017-04-02 fix component rotations and wire endpoints
2017-04-03 footprint and DRC fixes
2017-04-03 add power-plane cutouts
2017-04-03 add small polygons
2017-04-04 fix nearly all DRC errors
2017-04-04 place vias
2017-04-04 add thermal vias to footprints
2017-04-05 all nets connected
2017-04-05 layout passes DRC
2017-04-05 adjust polygons to be close to former gEDA layout
2017-04-06 more adjustments on copper layers
2017-04-06 position text on bottom silkscreen
2017-04-07 top silkscreen
2017-04-07 silkscreen descriptive text
2017-04-07 add silkscreen logo graphics
2017-04-08 make silkscreen sizes consistent
2017-04-08 postprocess vias to make them "encroached" or "semi-tented"
2017-04-10 CAM outputs: position file, BOM
2017-04-10 add schematic PDF and BOM
2017-04-10 changeover to KiCad complete. Remove gEDA schematic and layout
2017-04-10 add page titles to schematic
2017-04-14 fix firmware bugs in ADC and downconverter configuration
2017-04-16 support third RF channel---Ethernet payload now 840 Mbit/s
2017-04-16 remove unneeded FPGA tests
2017-04-17 use dither; improve DC compensation; put I and Q the right way around
2017-04-18 support 64-byte Ethernet command packets (rx)
2017-04-19 support 64-byte Ethernet status packets (tx), interleaved with main payload
2017-04-19 fix wrong clock on packet tx
2017-04-19 Ethernet inter-packet gap (IPG) should be 12 octets
2017-04-19 implement remaining Ethernet access functions for peripherals
2017-04-20 rework the polling code for clarity
2017-04-21 allow arbitrary locations for flash writes (for FPGA bitstream revisions over Ethernet) use a packet-based scheme for flash configuration parameters include additional sampling modes
2017-04-22 fix typo in flash configuration reads
2017-05-10 clean up timestamp handling; don't skip starting packets unnecessarily
2019-01-08 increase strength of ADC output drivers. On about 5% of the ADC-->FPGA links there were a few bit errors
2019-01-15 add a version number to firmware command set
2024-06-02 add Ethernet-based control, status, and frequency setting
2024-07-21 fpga/firmware/io.c: remove C lint
    Make it compile without complaint under gcc -Wall -Wextra
2024-07-21 fpga/firmware/cmd.c: remove C lint
    Rename process_eth_packet's addr as raddr, so it can build without complaint using -Wshadow
2024-07-21 fpga/xilinx/chip.ucf: separate clock groups
    Separating 125 MHz Ethernet clock from 38.88 MHz CPU clock
    gives the timing constraints half a chance of doing the right thing.
2024-07-21 fpga/hdl: remove some simple Verilog lint
    Now can be processed (almost) without warnings by
    iverilog -Wall -Wno-timescale -DSIMULATE top.v
    some residual complaints about picorv32.v, but that can't be helped
2024-07-22 Add tests in fpga/hdl
    Functional regression test for packet_rx
    Overall syntax check for top
    Expected output:
    $ make
    iverilog -o top_check -Wall -Wno-timescale -DSIMULATE top.v
    ./picorv32.v:1308: warning: @* is sensitive to all 32 words in array 'cpuregs'.
2024-07-22 fpga/hdl/packet_rx.v: pipeline comparisons
    Still passes regression test
    Should make timing better on hardware
2024-07-22 Churn in Makefiles
    xilinx/Makefile: use filenames as targets, and capture some dependencies
    firmware/Makefile: rearrange make and gcc configuration to work better with
    stock Debian gcc-riscv64-unknown-elf; do that with make TOOL_BASE=riscv64
    firmware/Makefile: add more warning gcc flags: -Wall -Wextra -Wshadow
2024-07-22 uart.v: rename bit to bit1, to avoid confusing SV-compatible parsers (like Verilator)
2024-07-22 Add cdc_snitch support
    Makefile rules and top skin, but not the cdc_snitch scripts themselves.
    No attempt to clean up CDC behavior.
    Result:
    OK1: 6046 CDC: 75 OKX: 153 BAD: 362
2024-07-22 Put in some simple clock-domain crossings
    New result:
    OK1: 6403 CDC: 75 OKX: 89 BAD: 82
